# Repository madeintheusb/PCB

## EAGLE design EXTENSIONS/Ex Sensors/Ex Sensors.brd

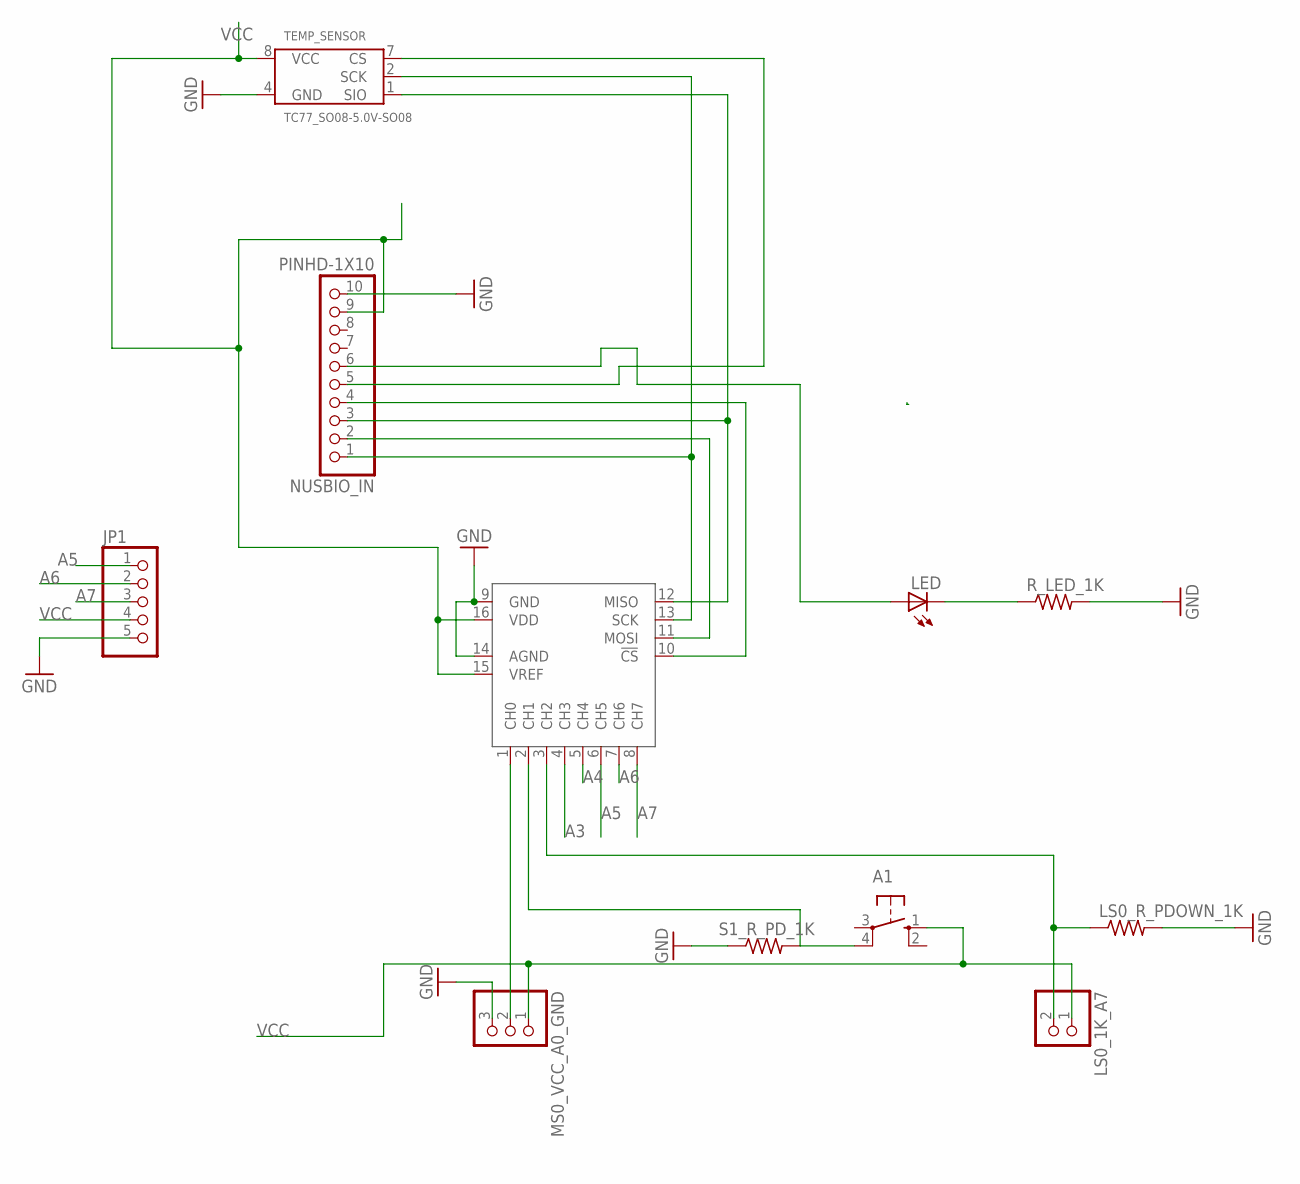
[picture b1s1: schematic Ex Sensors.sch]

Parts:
A1: 10-XX; B3F-10XX
JP1: PINHD-1X5; 1X05
LED: LEDCHIPLED_0805; CHIPLED_0805
LS0_1K_A7: PINHD-1X2; 1X02
LS0_R_PDOWN_1K: R-US_R0805; R0805
MS0_VCC_A0_GND: PINHD-1X3; 1X03
NUSBIO_IN: PINHD-1X10; 1X10-BIG
R_LED_1K: R-US_R0805; R0805
S1_R_PD_1K: R-US_R0805; R0805
TEMP_SENSOR: TC77_SO08-5.0V-SO08; SO-08
U$1: MCP3008SL; SO16

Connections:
A3: U$1.4 (CH3)
A4: U$1.5 (CH4)
A5: JP1.1, U$1.6 (CH5)
A6: JP1.2, U$1.7 (CH6)
A7: JP1.3, U$1.8 (CH7)
GND: JP1.5, LS0_R_PDOWN_1K.2, MS0_VCC_A0_GND.3, NUSBIO_IN.10, R_LED_1K.2, S1_R_PD_1K.1, TEMP_SENSOR.4 (GND), U$1.9 (GND), U$1.14 (AGND)
unnamed: NUSBIO_IN.1, TEMP_SENSOR.2 (SCK), U$1.13 (SCK)
unnamed: NUSBIO_IN.2, U$1.11 (MOSI)
unnamed: NUSBIO_IN.3, TEMP_SENSOR.1 (SIO), U$1.12 (MISO)
unnamed: NUSBIO_IN.5, TEMP_SENSOR.7 (CS)
unnamed: NUSBIO_IN.4, U$1.10 (!CS)
unnamed: LED.C, R_LED_1K.1
unnamed: LED.A, NUSBIO_IN.6
unnamed: MS0_VCC_A0_GND.2, U$1.1 (CH0)
unnamed: LS0_1K_A7.2, LS0_R_PDOWN_1K.1, U$1.3 (CH2)
unnamed: A1.4 (P1), S1_R_PD_1K.2, U$1.2 (CH1)
VCC: A1.1 (S), JP1.4, LS0_1K_A7.1, MS0_VCC_A0_GND.1, NUSBIO_IN.9, TEMP_SENSOR.8 (VCC), U$1.15 (VREF), U$1.16 (VDD)

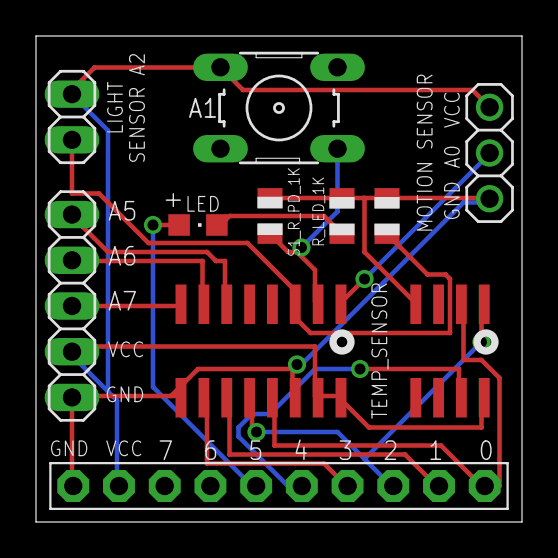
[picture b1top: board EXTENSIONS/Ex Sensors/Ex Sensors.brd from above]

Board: 2 copper layers, 27.0 x 27.0 mm, 11 parts (0 on the bottom side), 15 nets.

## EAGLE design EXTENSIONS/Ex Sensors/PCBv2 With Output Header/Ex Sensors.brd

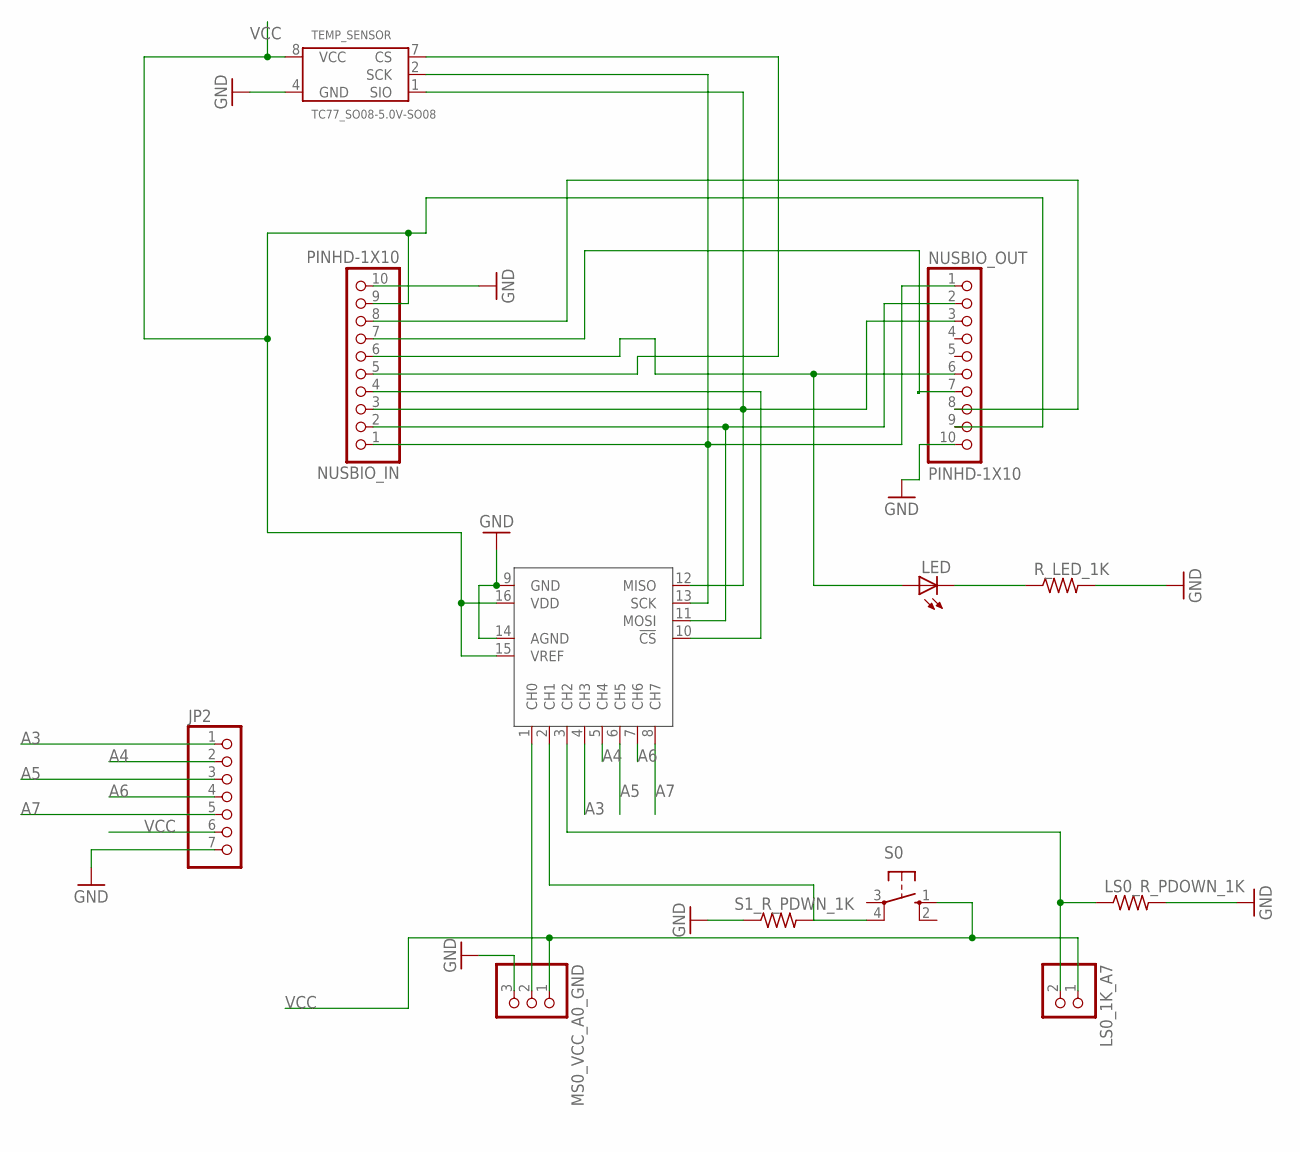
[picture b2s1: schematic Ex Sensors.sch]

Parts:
JP2: PINHD-1X7; 1X07
LED: LEDCHIPLED_0805; CHIPLED_0805
LS0_1K_A7: PINHD-1X2; 1X02
LS0_R_PDOWN_1K: R-US_R0805; R0805
MS0_VCC_A0_GND: PINHD-1X3; 1X03
NUSBIO_IN: PINHD-1X10; 1X10-BIG
NUSBIO_OUT: PINHD-1X10; 1X10-BIG
R_LED_1K: R-US_R0805; R0805
S0: 10-XX; B3F-10XX
S1_R_PDWN_1K: R-US_R0805; R0805
TEMP_SENSOR: TC77_SO08-5.0V-SO08; SO-08
U$1: MCP3008SL; SO16

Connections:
A3: JP2.1, U$1.4 (CH3)
A4: JP2.2, U$1.5 (CH4)
A5: JP2.3, U$1.6 (CH5)
A6: JP2.4, U$1.7 (CH6)
A7: JP2.5, U$1.8 (CH7)
GND: JP2.7, LS0_R_PDOWN_1K.2, MS0_VCC_A0_GND.3, NUSBIO_IN.10, NUSBIO_OUT.10, R_LED_1K.2, S1_R_PDWN_1K.1, TEMP_SENSOR.4 (GND), U$1.9 (GND), U$1.14 (AGND)
unnamed: NUSBIO_IN.1, NUSBIO_OUT.1, TEMP_SENSOR.2 (SCK), U$1.13 (SCK)
unnamed: NUSBIO_IN.2, NUSBIO_OUT.2, U$1.11 (MOSI)
unnamed: NUSBIO_IN.3, NUSBIO_OUT.3, TEMP_SENSOR.1 (SIO), U$1.12 (MISO)
unnamed: NUSBIO_IN.5, TEMP_SENSOR.7 (CS)
unnamed: NUSBIO_IN.4, U$1.10 (!CS)
unnamed: LED.C, R_LED_1K.1
unnamed: LED.A, NUSBIO_IN.6, NUSBIO_OUT.6
unnamed: NUSBIO_IN.7, NUSBIO_OUT.7
unnamed: NUSBIO_IN.8, NUSBIO_OUT.8
unnamed: MS0_VCC_A0_GND.2, U$1.1 (CH0)
unnamed: LS0_1K_A7.2, LS0_R_PDOWN_1K.1, U$1.3 (CH2)
unnamed: S0.4 (P1), S1_R_PDWN_1K.2, U$1.2 (CH1)
VCC: JP2.6, LS0_1K_A7.1, MS0_VCC_A0_GND.1, NUSBIO_IN.9, NUSBIO_OUT.9, S0.1 (S), TEMP_SENSOR.8 (VCC), U$1.15 (VREF), U$1.16 (VDD)

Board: 2 copper layers, 12 parts (0 on the bottom side), 19 nets, no tracks yet.

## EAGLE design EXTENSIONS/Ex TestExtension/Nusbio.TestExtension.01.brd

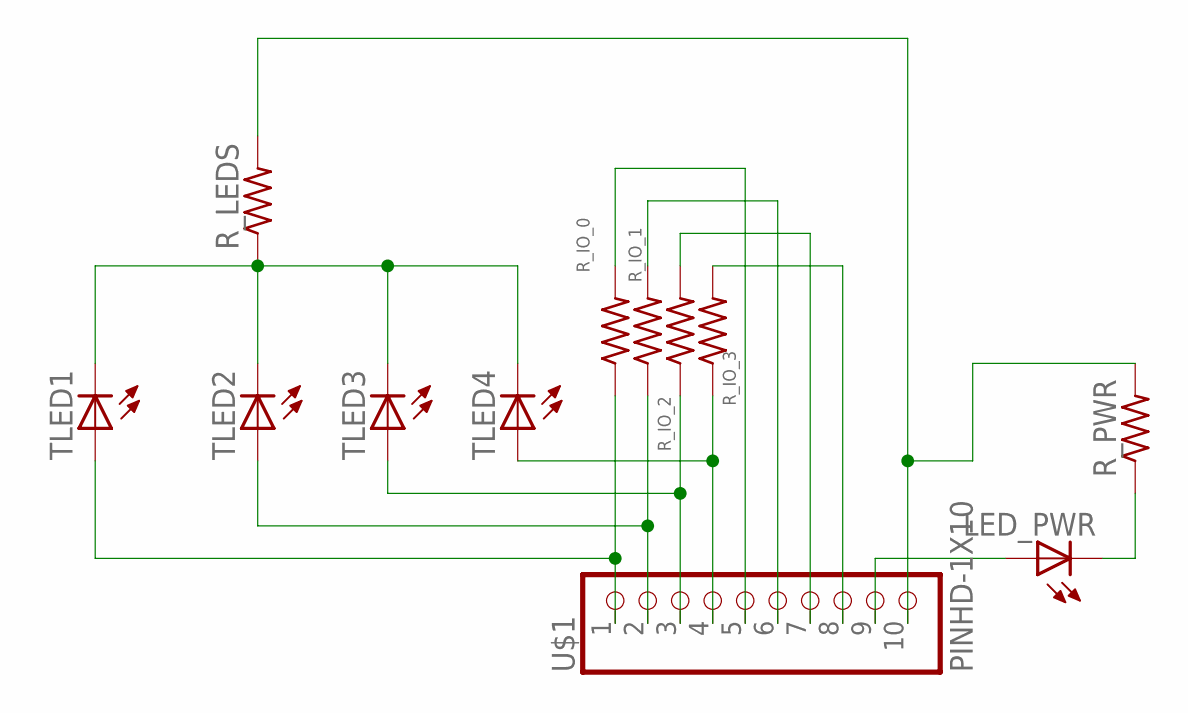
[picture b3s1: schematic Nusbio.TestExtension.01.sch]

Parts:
LED_PWR: LEDSMT1206; 1206
R_IO_0, R_IO_1, R_IO_2, R_IO_3: R-US_R1206; R1206
R_LEDS: R-US_R1206; R1206
R_PWR: R-US_R1206; R1206
TLED1, TLED2, TLED3, TLED4: LEDSMT1206; 1206
U$1: PINHD-1X10; 1X10-BIG

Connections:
unnamed: R_IO_3.2, U$1.8
unnamed: R_LEDS.1, TLED1.C, TLED2.C, TLED3.C, TLED4.C
unnamed: R_LEDS.2, R_PWR.2, U$1.10
unnamed: LED_PWR.A, U$1.9
unnamed: LED_PWR.C, R_PWR.1
unnamed: R_IO_3.1, TLED4.A, U$1.4
unnamed: R_IO_0.1, TLED1.A, U$1.1
unnamed: R_IO_2.2, U$1.7
unnamed: R_IO_1.2, U$1.6
unnamed: R_IO_0.2, U$1.5
unnamed: R_IO_2.1, TLED3.A, U$1.3
unnamed: R_IO_1.1, TLED2.A, U$1.2

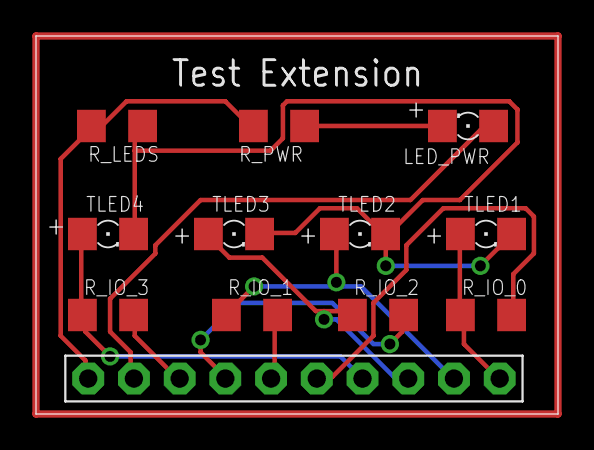
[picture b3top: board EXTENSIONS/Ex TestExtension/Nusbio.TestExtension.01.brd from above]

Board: 2 copper layers, 29.0 x 21.0 mm, 12 parts (0 on the bottom side), 12 nets.

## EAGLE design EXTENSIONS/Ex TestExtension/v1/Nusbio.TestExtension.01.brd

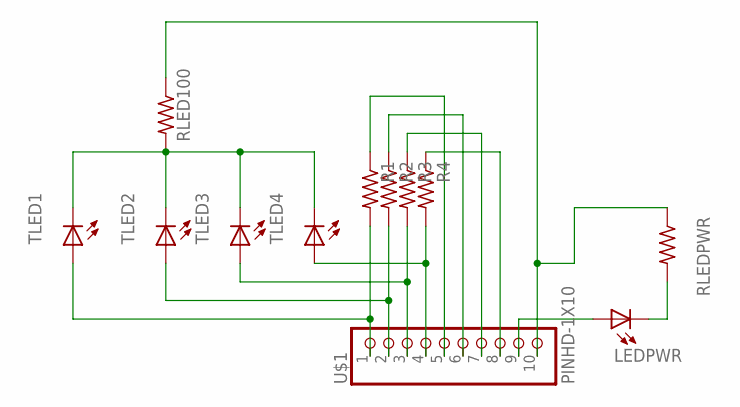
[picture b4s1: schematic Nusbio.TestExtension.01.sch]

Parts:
LEDPWR: LEDCHIPLED_0805; CHIPLED_0805
R1, R2, R3, R4: R-US_R0805; R0805
RLED100: R-US_R0805; R0805
RLEDPWR: R-US_R0805; R0805
TLED1, TLED2, TLED3, TLED4: LEDCHIPLED_0805; CHIPLED_0805
U$1: PINHD-1X10; 1X10-BIG

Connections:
unnamed: R4.1, U$1.8
unnamed: RLED100.2, TLED1.C, TLED2.C, TLED3.C, TLED4.C
unnamed: RLED100.1, RLEDPWR.1, U$1.10
unnamed: LEDPWR.A, U$1.9
unnamed: LEDPWR.C, RLEDPWR.2
unnamed: R4.2, TLED4.A, U$1.4
unnamed: R1.2, TLED1.A, U$1.1
unnamed: R3.1, U$1.7
unnamed: R2.1, U$1.6
unnamed: R1.1, U$1.5
unnamed: R3.2, TLED3.A, U$1.3
unnamed: R2.2, TLED2.A, U$1.2

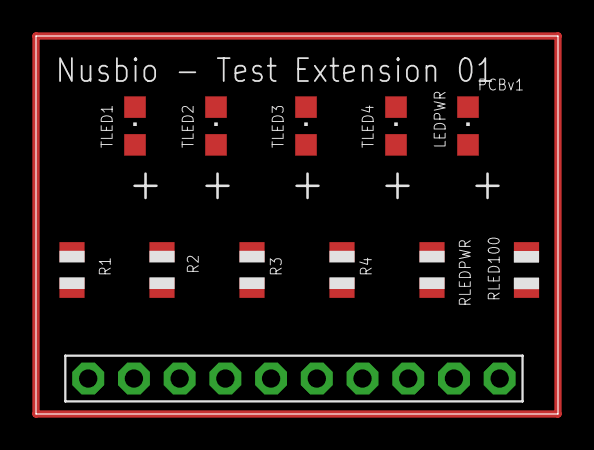
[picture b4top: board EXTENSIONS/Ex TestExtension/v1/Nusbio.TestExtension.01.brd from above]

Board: 2 copper layers, 29.0 x 21.0 mm, 12 parts (0 on the bottom side), 12 nets.
